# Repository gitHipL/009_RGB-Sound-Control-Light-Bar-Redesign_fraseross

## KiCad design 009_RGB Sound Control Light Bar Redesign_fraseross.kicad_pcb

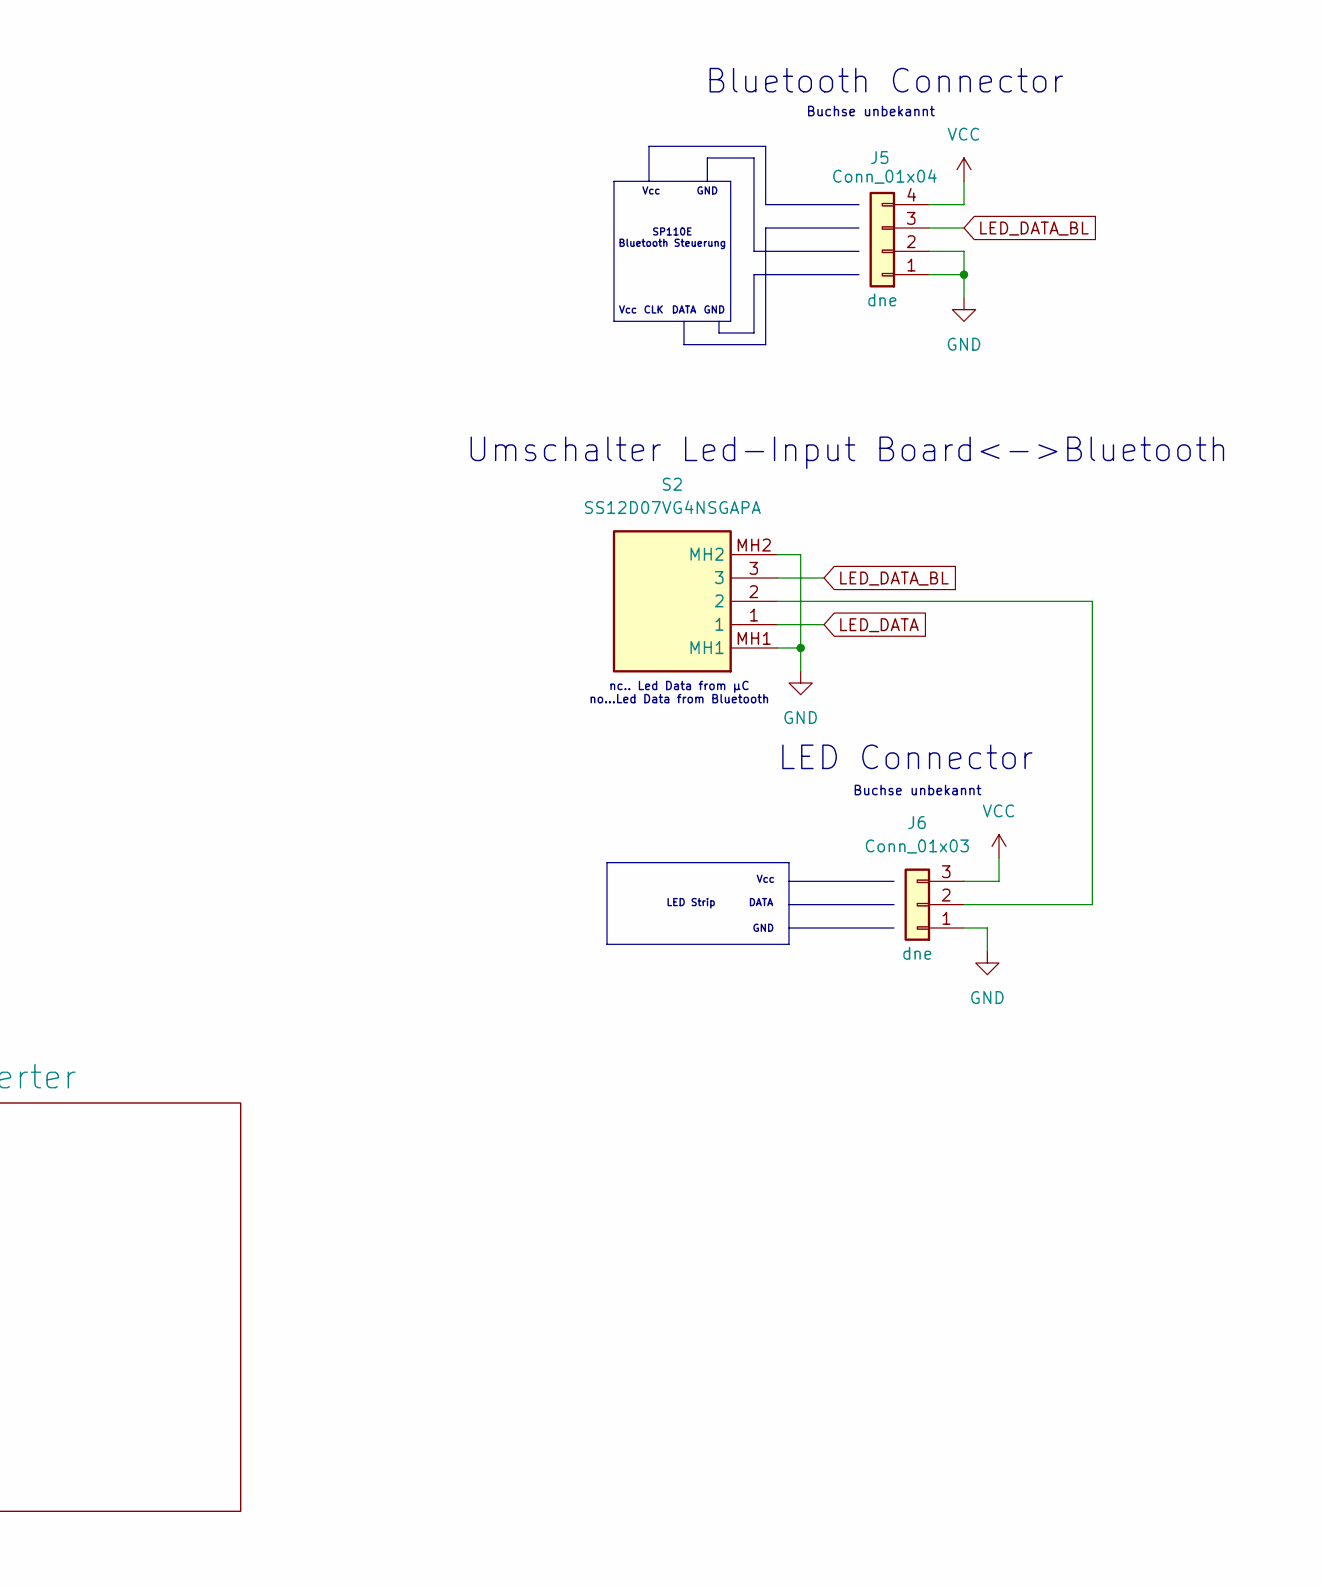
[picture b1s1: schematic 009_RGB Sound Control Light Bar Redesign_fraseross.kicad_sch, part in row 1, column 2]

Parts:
J5: Conn_01x04; PinSocket_1x04_P1.00mm_Vertical
J6: Conn_01x03; PinSocket_1x03_P1.00mm_Vertical
S2: SS12D07VG4NSGAPA; Manufacturer_Part_Number SS12D07VG4NSGAPA; Mouser Part Number N/A

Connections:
GND: J5.1, J5.2, J6.1, S2.MH1, S2.MH2; also elsewhere on the board
LED_DATA: S2.1; also elsewhere on the board
LED_DATA_BL: J5.3, S2.3
unnamed: J6.2, S2.2
VCC: J5.4, J6.3; also elsewhere on the board

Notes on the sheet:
Vcc
GND
Buchse unbekannt
LED Connector
Umschalter Led-Input Board<->Bluetooth
nc.. Led Data from µC no...Led Data from Bluetooth
DATA
CLK
Bluetooth Connector
SP110E Bluetooth Steuerung
LED Strip

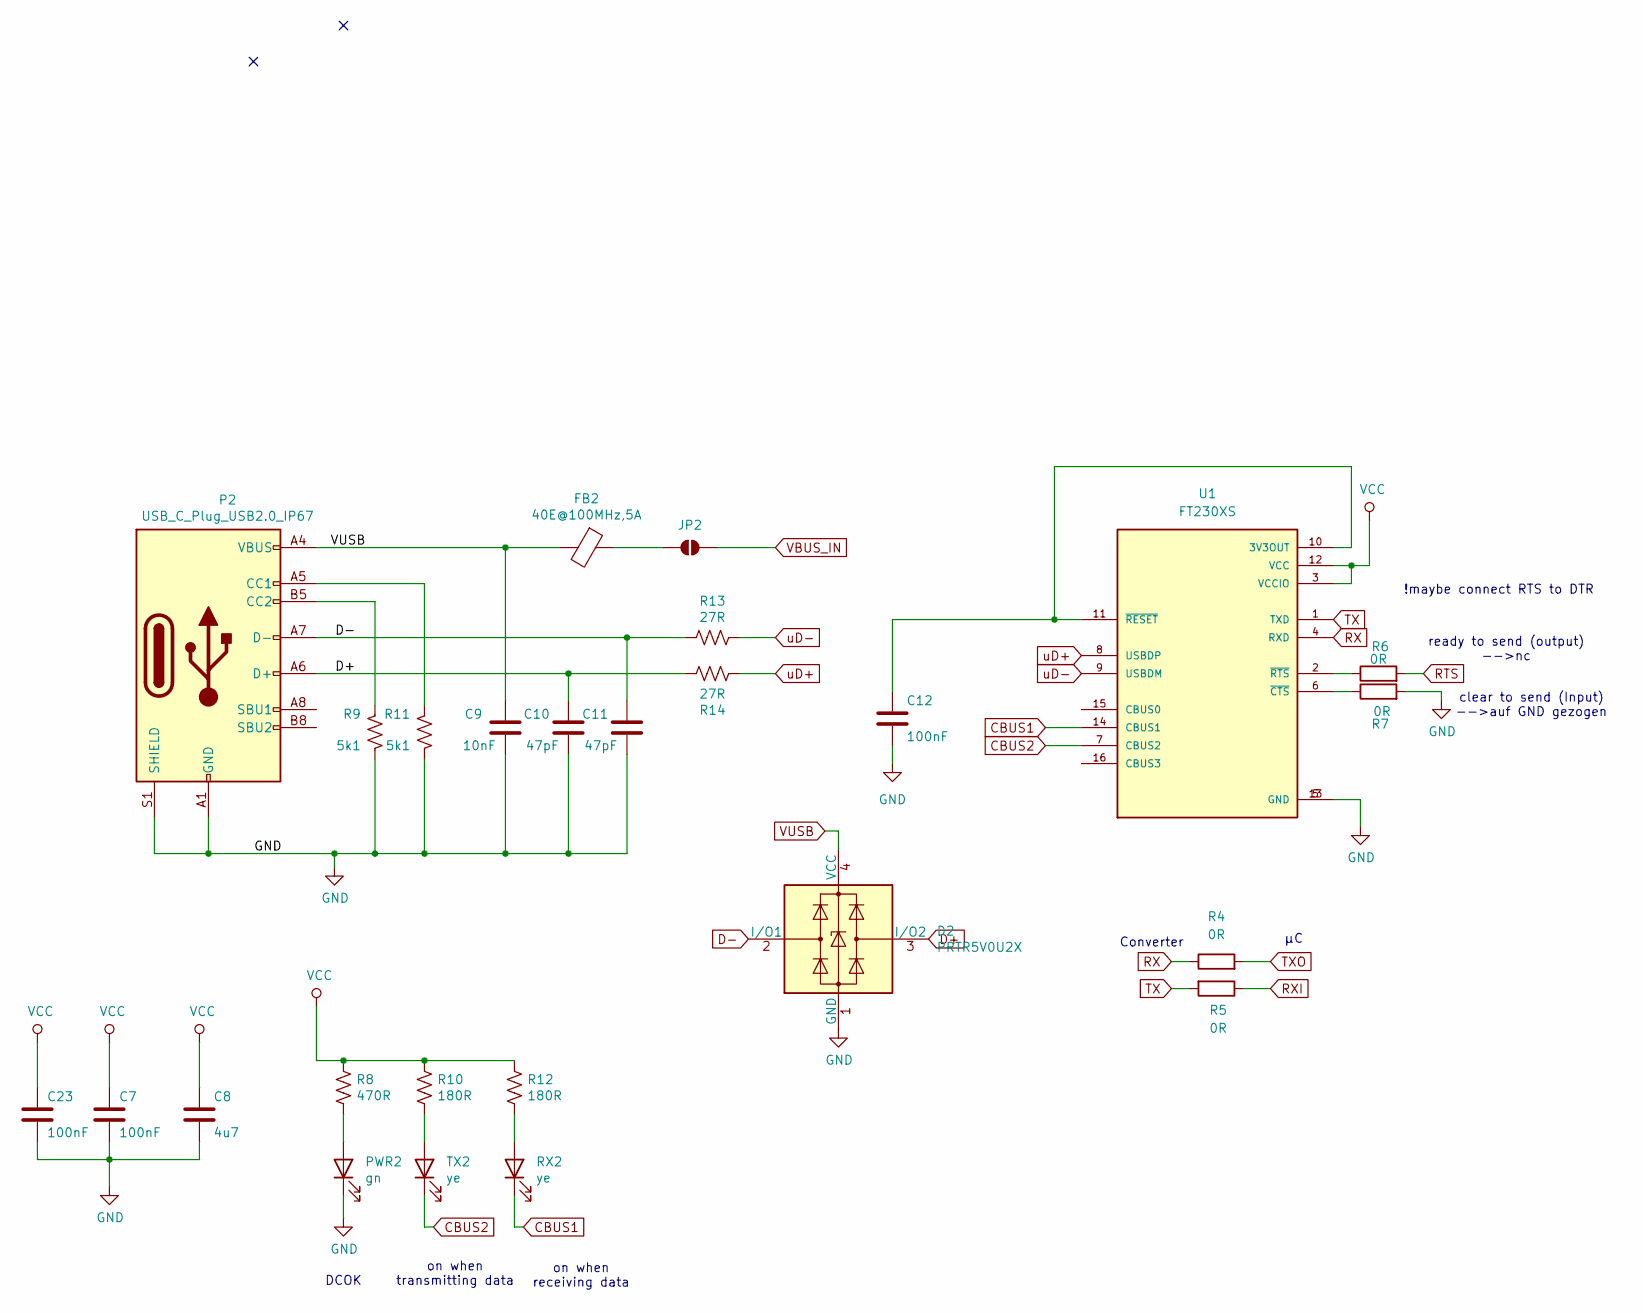
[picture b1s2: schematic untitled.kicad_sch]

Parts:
C7, C12, C23: 100nF; C_0603_1608Metric; Part C42998
C8: 4u7; C_0805_2012Metric; Part C87998
C9: 10nF; C_0603_1608Metric; Part C100042
C10, C11: 47pF; C_0603_1608Metric; Part C105622
D2: PRTR5V0U2X; SOT-143; LCSC PN C12333
FB2: 40E@100MHz,5A; L_0805_2012Metric; LCSC PN C369522
JP2: SolderJumper_2_Open; SolderJumper-2_P1.3mm_Bridged_RoundedPad1.0x1.5mm
P2: USB_C_Plug_USB2.0_IP67; GCT_USB4730-GF-A_REVA; Part USB4730-GF-A
PWR2: gn; LED_0603_1608Metric; LCSC PN C19171301
R4, R5, R6, R7: 0R; R_0603_1608Metric
R8: 470R; R_0603_1608Metric; LCSC C19171301
R9, R11: 5k1; R_0603_1608Metric; Part C332117
R10, R12: 180R; R_0603_1608Metric; Part C25585
R13, R14: 27R; R_0603_1608Metric; Part C325726
RX2: ye; LED_0603_1608Metric; LCSC PN C965802
TX2: ye; LED_0603_1608Metric; LCSC PN C965802
U1: FT230XS; SSOP-16_3.9x4.9mm_P0.635mm; PARTREV 1.5; LCSC PN C69082

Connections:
CBUS1: RX2.1 (K), U1.14 (CBUS1); also elsewhere on the board
CBUS2: TX2.1 (K), U1.7 (CBUS2); also elsewhere on the board
D+: C10.1, D2.3 (I/O2), P2.A6 (D+), P2.B6 (D+), R14.2
D-: C11.1, D2.2 (I/O1), P2.A7 (D-), P2.B7 (D-), R13.1
GND: C7.2, C8.2, C9.2, C10.2, C11.2, C12.2, C23.2, D2.1 (GND), P2.A1 (GND), P2.S1 (SHIELD), PWR2.1 (K), R7.2, R9.2, R11.2, U1.5 (GND), U1.13 (GND); also elsewhere on the board
unnamed: FB2.1, JP2.1 (A)
unnamed: P2.A5 (CC1), R11.1
unnamed: P2.B5 (CC2), R9.1
unnamed 32: PWR2.2 (A), R8.2; also elsewhere on the board
unnamed 33: R12.2, RX2.2 (A); also elsewhere on the board
unnamed 35: R10.2, TX2.2 (A); also elsewhere on the board
unnamed: C12.1, U1.10 (3V3OUT), U1.11 (~RESET)
unnamed: R7.1, U1.6 (~CTS)
unnamed: R6.1, U1.2 (~RTS)
RTS: R6.2; also elsewhere on the board
RX: R4.1, U1.4 (RXD)
RXI: R5.1; also elsewhere on the board
TX: R5.2, U1.1 (TXD)
TXO: R4.2; also elsewhere on the board
VBUS_IN: JP2.2 (B); also elsewhere on the board
VCC: C7.1, C8.1, C23.1, R8.1, R10.1, R12.1, U1.3 (VCCIO), U1.12 (VCC); also elsewhere on the board
VUSB: C9.1, D2.4 (VCC), FB2.2, P2.A4 (VBUS)
uD+: R14.1, U1.8 (USBDP)
uD-: R13.2, U1.9 (USBDM)

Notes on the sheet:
on when receiving data
DCOK
ready to send (output) -->nc
on when transmitting data
Converter
clear to send (Input) -->auf GND gezogen
!maybe connect RTS to DTR

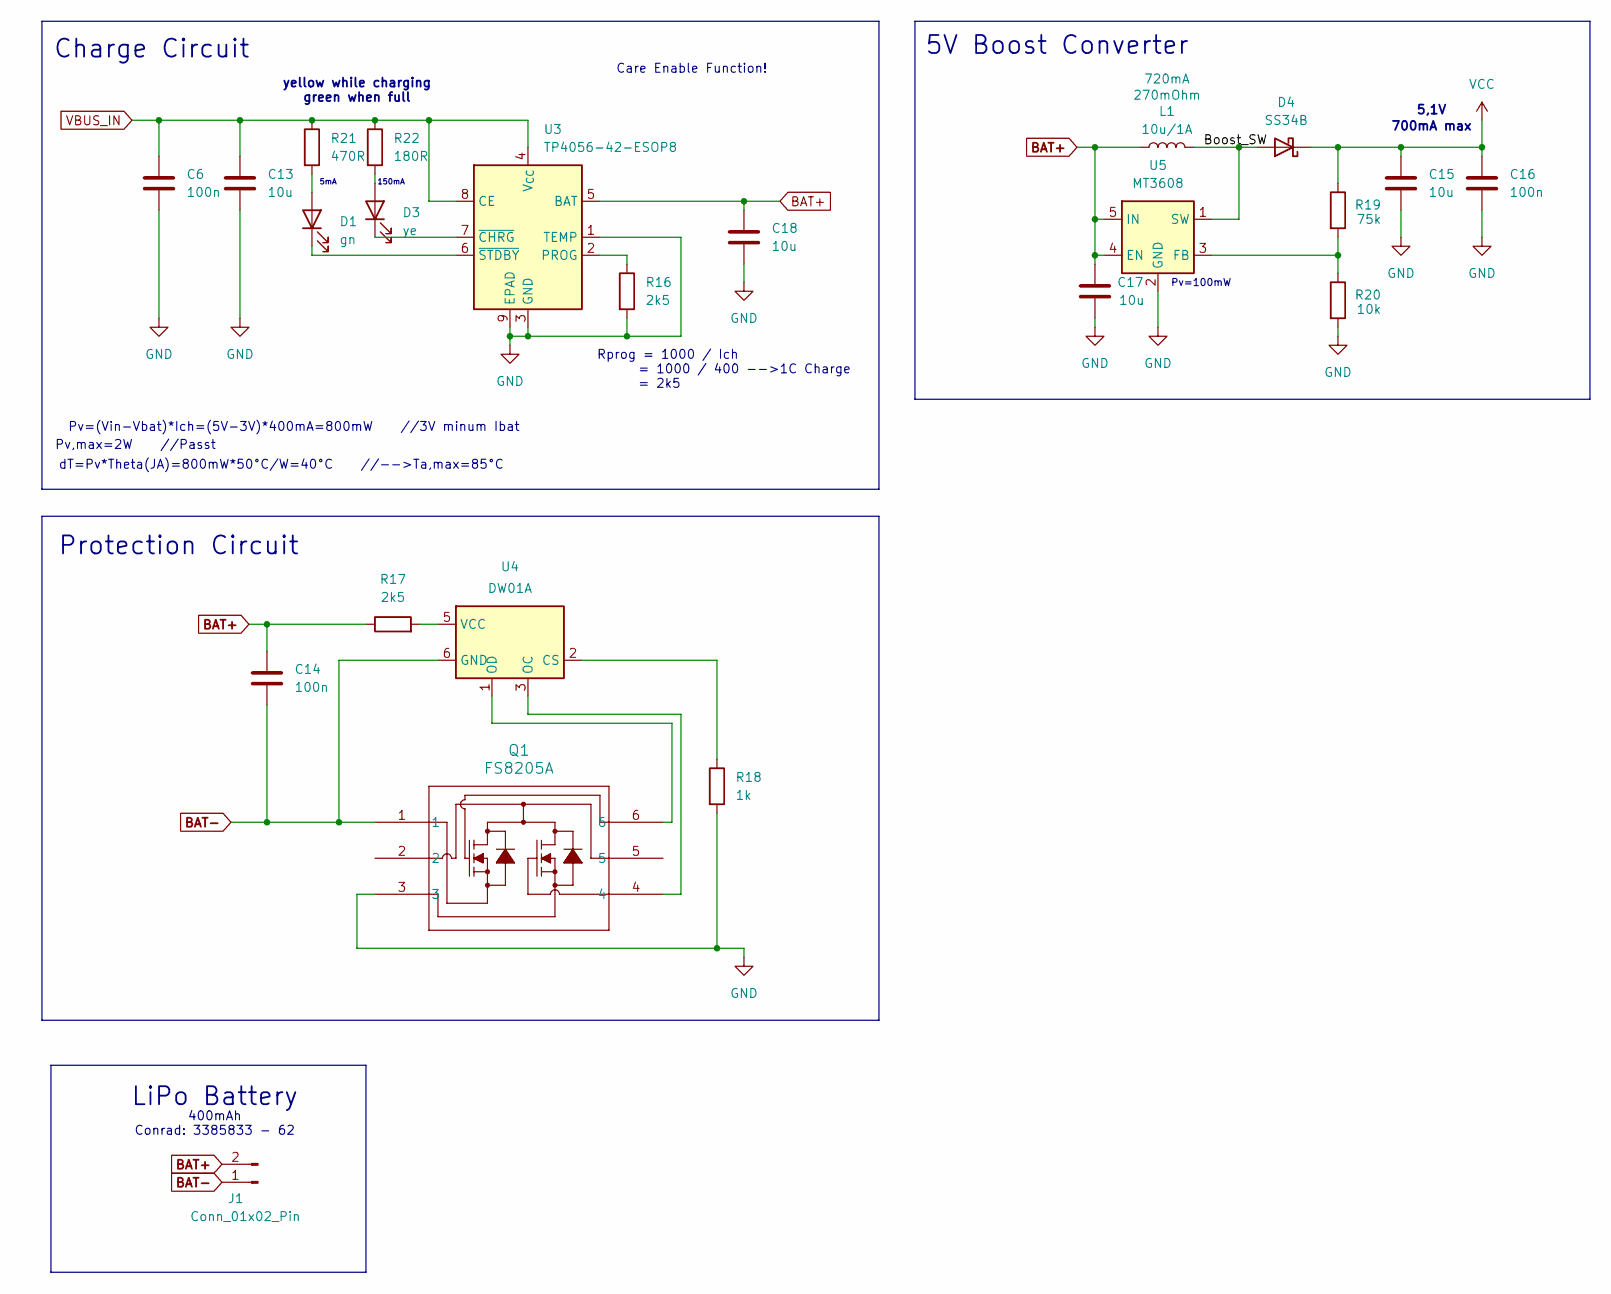
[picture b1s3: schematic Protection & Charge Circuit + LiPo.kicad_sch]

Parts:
C6, C14, C16: 100n; C_0603_1608Metric
C13, C18: 10u; C_0603_1608Metric
C15, C17: 10u; C_0805_2012Metric
D1: gn; LED_0603_1608Metric; LCSC PN C19171301
D3: ye; LED_0603_1608Metric; LCSC PN C965802
D4: SS34B; D_SMB; LCSC PN C13762
J1: Conn_01x02_Pin; PinHeader_1x02_P2.54mm_Vertical
L1: 10u/1A; L_Coilcraft_LPS3010; LCSC C280522
Q1: FS8205A; SOT-23-6; LCSC PN C2830320
R16: 2k5; R_0603_1608Metric
R17: 2k5; R_0805_2012Metric
R18: 1k; R_0603_1608Metric
R19: 75k; R_0603_1608Metric
R20: 10k; R_0603_1608Metric
R21: 470R; R_0603_1608Metric
R22: 180R; R_0603_1608Metric
U3: TP4056-42-ESOP8; SOIC-8-1EP_3.9x4.9mm_P1.27mm_EP2.41x3.3mm_ThermalVias; LCSC PN C725790
U4: DW01A; SOT-23-6; LCSC PN C2927799
U5: MT3608; SOT-23-6; LCSC PN C84817

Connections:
/Power/Boost_SW: D4.2 (A), L1.2, U5.1 (SW)
BAT+: C14.2, C17.1, C18.2, J1.2, L1.1, R17.1, U3.5 (BAT), U5.4 (EN), U5.5 (IN)
BAT-: C14.1, J1.1, Q1.1, U4.6 (GND)
GND: C6.1, C13.1, C15.2, C16.2, C17.2, C18.1, Q1.3, R16.2, R18.2, R20.2, U3.1 (TEMP), U3.3 (GND), U3.9 (EPAD), U5.2 (GND); also elsewhere on the board
unnamed: D1.2 (A), R21.2
unnamed: D1.1 (K), U3.6 (~STDBY)
unnamed: D3.2 (A), R22.2
unnamed: D3.1 (K), U3.7 (~CHRG)
unnamed: R16.1, U3.2 (PROG)
unnamed: R18.1, U4.2 (CS)
unnamed: Q1.4, U4.3 (OC)
unnamed: Q1.6, U4.1 (OD)
unnamed: R17.2, U4.5 (VCC)
unnamed: R19.2, R20.1, U5.3 (FB)
VBUS_IN: C6.2, C13.2, R21.1, R22.1, U3.4 (V_{CC}), U3.8 (CE); also elsewhere on the board
VCC: C15.1, C16.1, D4.1 (K), R19.1; also elsewhere on the board

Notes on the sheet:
400mAh Conrad: 3385833 - 62
LiPo Battery
dT=Pv*Theta(JA)=800mW*50°C/W=40°C //-->Ta,max=85°C
yellow while charging green when full
Rprog = 1000 / Ich = 1000 / 400 -->1C Charge = 2k5
5mA
5V Boost Converter
150mA
Pv=100mW
5,1V
700mA max
Protection Circuit
Care Enable Function!
Pv,max=2W //Passt
Charge Circuit
Pv=(Vin-Vbat)*Ich=(5V-3V)*400mA=800mW //3V minum Ibat

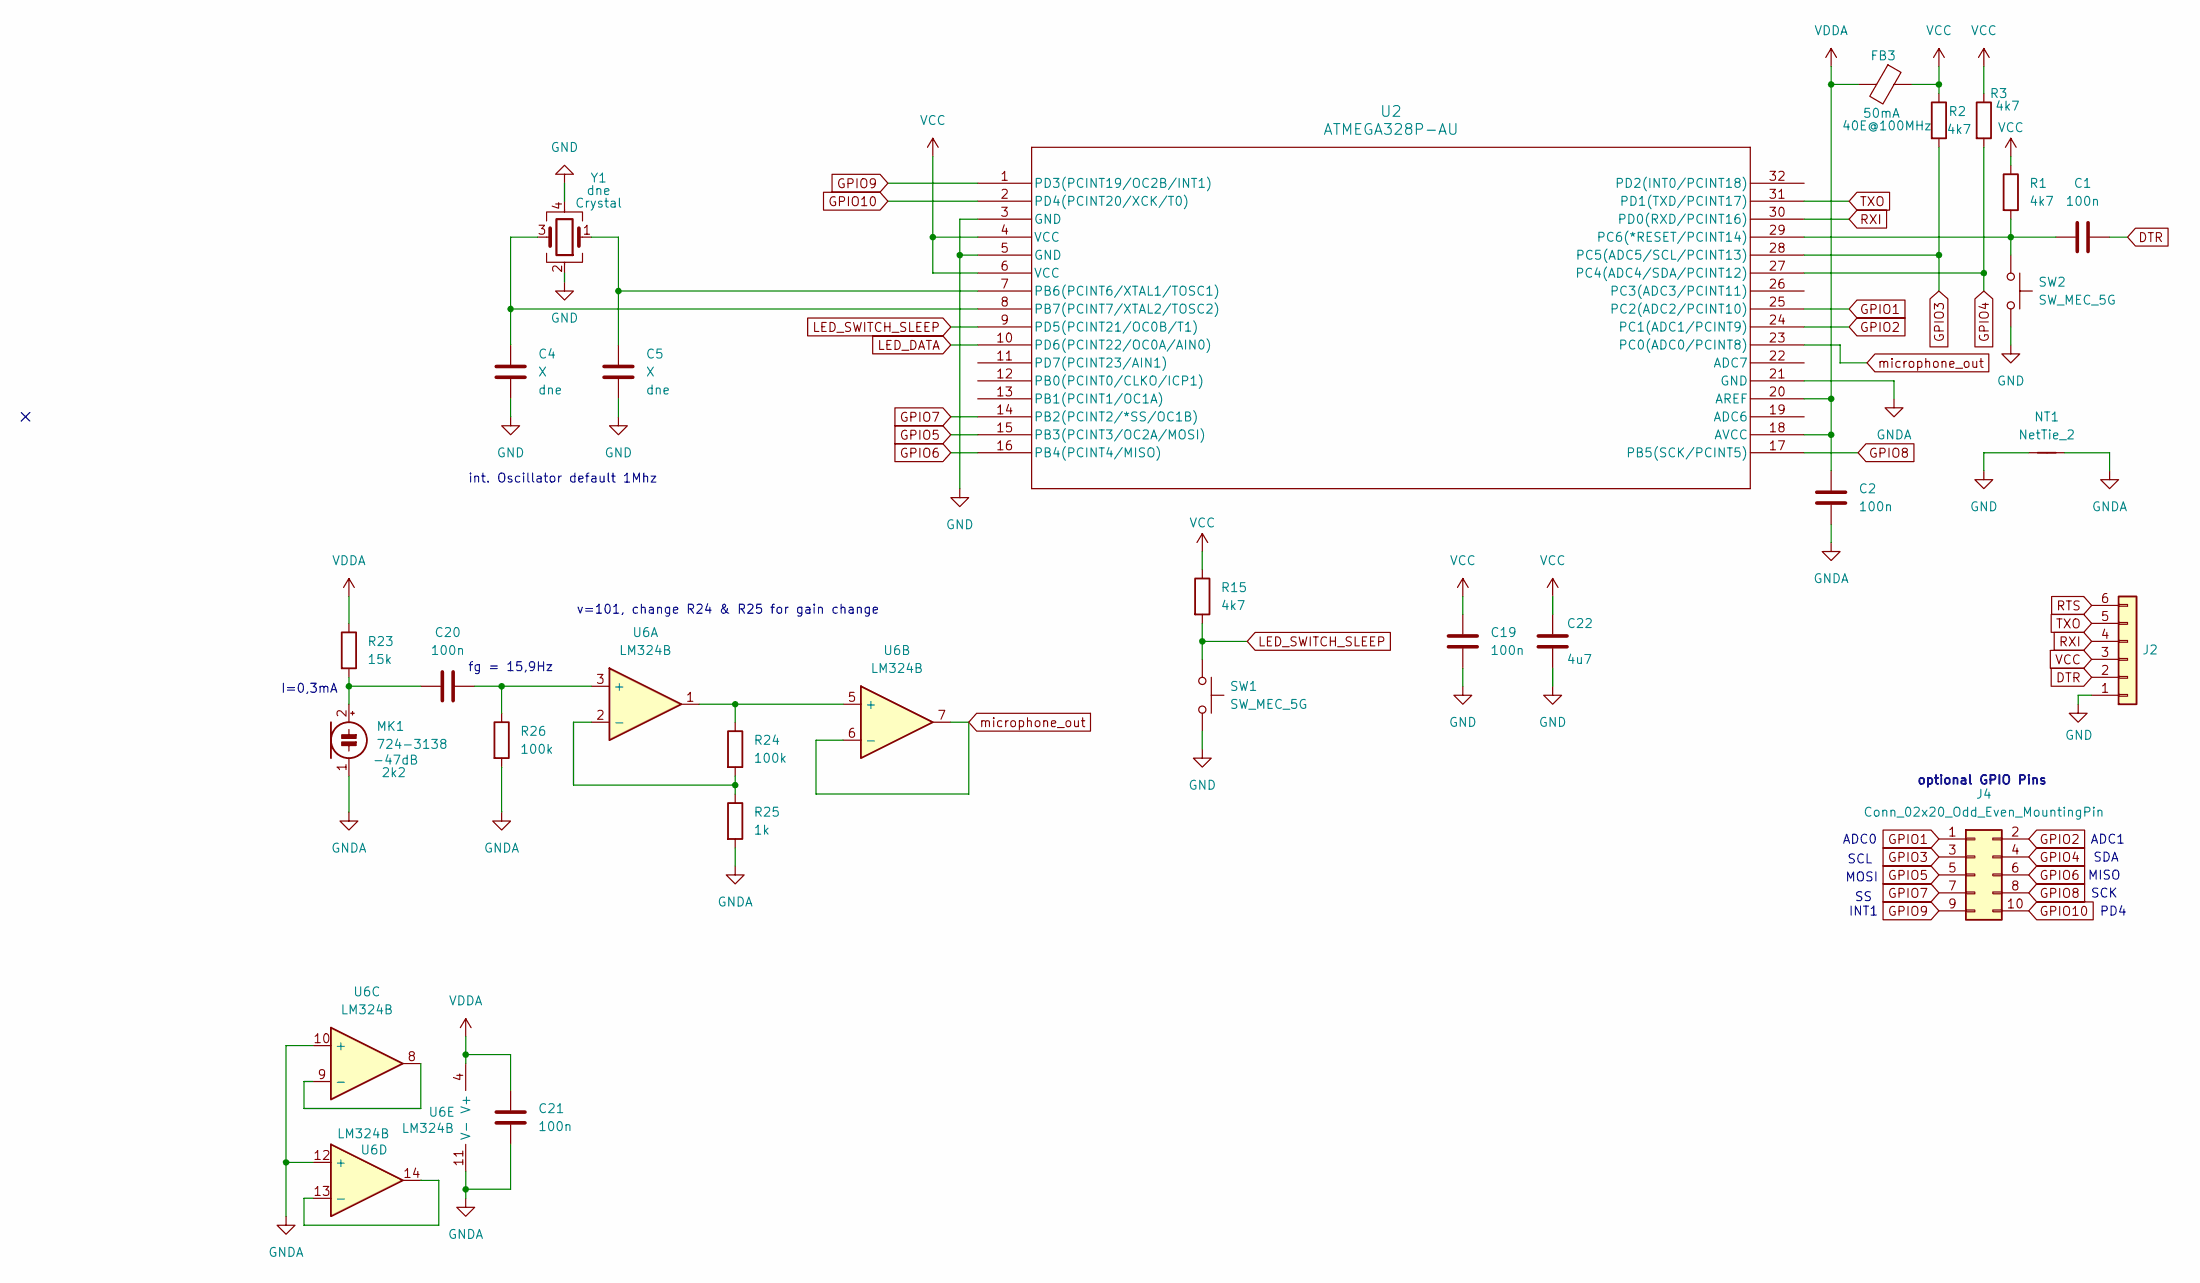
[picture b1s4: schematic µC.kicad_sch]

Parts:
C1, C2, C19, C20, C21: 100n; C_0603_1608Metric
C4, C5: X; C_0603_1608Metric
C22: 4u7; C_0805_2012Metric; Part C87998
FB3: 40E@100MHz; L_0603_1608Metric; LCSC PN C142073
J2: Conn_01x06; PinHeader_1x06_P2.54mm_Vertical
J4: Conn_02x20_Odd_Even_MountingPin; PinHeader_2x05_P1.00mm_Vertical_SMD
MK1: 724-3138; 724-3138 microphone RS Components
NT1: NetTie_2; NetTie-2_SMD_Pad0.5mm
R1, R2, R3, R15: 4k7; R_0603_1608Metric
R23: 15k; R_0603_1608Metric
R24, R26: 100k; R_0603_1608Metric
R25: 1k; R_0603_1608Metric
SW1: SW_MEC_5G; SW_K2-1112SW-A4SW-04_HRO; LCSC PN C223811
SW2: SW_MEC_5G; SW_Taster_C381039; LCSC C381039
U2: ATMEGA328P-AU; TQFP32_32A_MCH; LCSC PN C14877
U6: LM324B; TSSOP-14_4.4x5mm_P0.65mm; LCSC PN C5214225
Y1: Crystal; Crystal_SMD_Abracon_ABM8AIG-4Pin_3.2x2.5mm; LCSC PN C13738

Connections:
DTR: C1.2, J2.2
GND: C4.1, C5.1, C19.1, C22.2, J2.1, NT1.1, SW1.2 (B), SW2.2 (B), U2.3 (GND), U2.5 (GND), Y1.2, Y1.4; also elsewhere on the board
GNDA: C2.1, C21.1, MK1.1 (-), NT1.2, R25.2, R26.2, U2.21 (GND), U6.10 (+), U6.11 (V-), U6.12 (+)
GPIO1: J4.1, U2.25 (PC2(ADC2/PCINT10))
GPIO2: J4.2, U2.24 (PC1(ADC1/PCINT9))
GPIO3: J4.3, R2.2, U2.28 (PC5(ADC5/SCL/PCINT13))
GPIO4: J4.4, R3.2, U2.27 (PC4(ADC4/SDA/PCINT12))
GPIO5: J4.5, U2.15 (PB3(PCINT3/OC2A/MOSI))
GPIO6: J4.6, U2.16 (PB4(PCINT4/MISO))
GPIO7: J4.7, U2.14 (PB2(PCINT2/*SS/OC1B))
GPIO8: J4.8, U2.17 (PB5(SCK/PCINT5))
GPIO9: J4.9, U2.1 (PD3(PCINT19/OC2B/INT1))
GPIO10: J4.10, U2.2 (PD4(PCINT20/XCK/T0))
LED_DATA: U2.10 (PD6(PCINT22/OC0A/AIN0)); also elsewhere on the board
LED_SWITCH_SLEEP: R15.2, SW1.1 (A), U2.9 (PD5(PCINT21/OC0B/T1))
unnamed: C20.1, MK1.2 (+), R23.2
unnamed: C1.1, R1.2, SW2.1 (A), U2.29 (PC6(*RESET/PCINT14))
unnamed: C5.2, U2.7 (PB6(PCINT6/XTAL1/TOSC1)), Y1.1
unnamed: C4.2, U2.8 (PB7(PCINT7/XTAL2/TOSC2)), Y1.3
unnamed: C20.2, R26.1, U6.3 (+)
unnamed: R24.2, R25.1, U6.2 (-)
unnamed: R24.1, U6.1, U6.5 (+)
unnamed: U6.8, U6.9 (-)
unnamed: U6.13 (-), U6.14
RTS: J2.6; also elsewhere on the board
RXI: J2.4, U2.30 (PD0(RXD/PCINT16)); also elsewhere on the board
TXO: J2.5, U2.31 (PD1(TXD/PCINT17)); also elsewhere on the board
VCC: C19.2, C22.1, FB3.1, J2.3, R1.1, R2.1, R3.1, R15.1, U2.4 (VCC), U2.6 (VCC); also elsewhere on the board
VDDA: C2.2, C21.2, FB3.2, R23.1, U2.18 (AVCC), U2.20 (AREF), U6.4 (V+)
microphone_out: U2.23 (PC0(ADC0/PCINT8)), U6.6 (-), U6.7

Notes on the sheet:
SCL
I=0,3mA
INT1
ADC1
PD4
SDA
optional GPIO Pins
v=101, change R24 & R25 for gain change
MISO
ADC0
int. Oscillator default 1Mhz
fg = 15,9Hz
MOSI
SCK

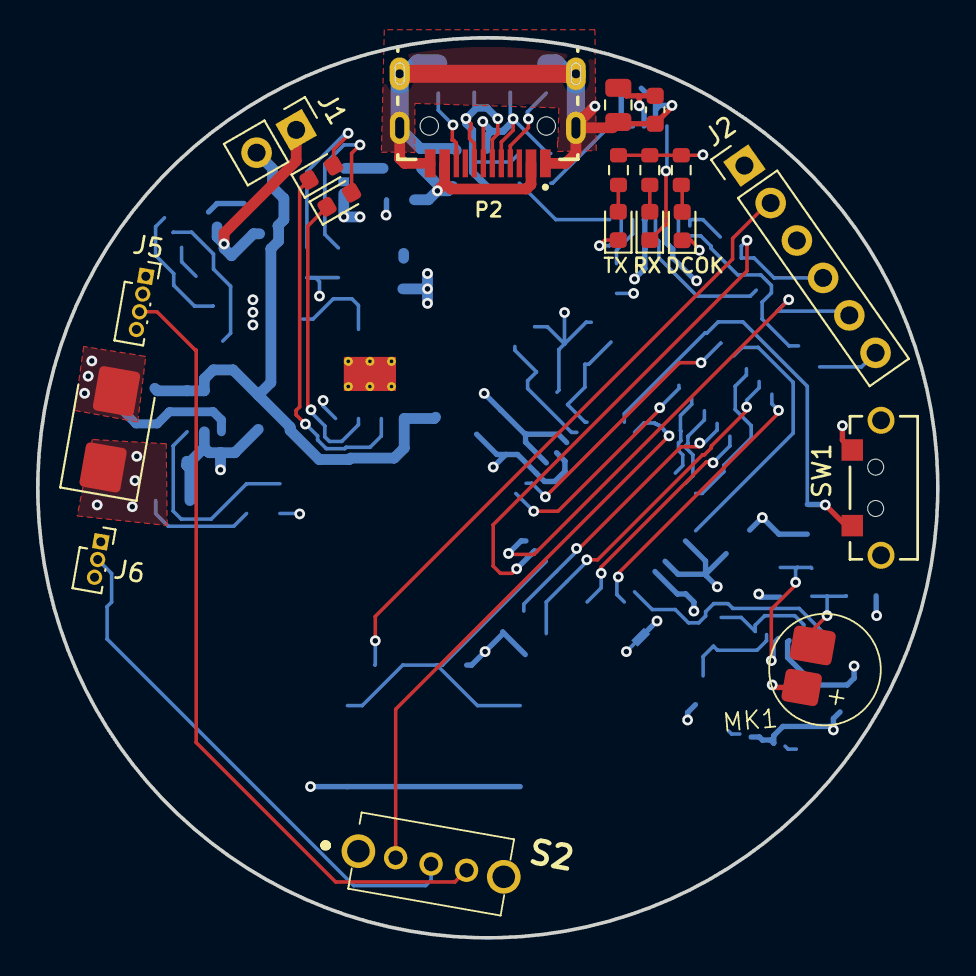
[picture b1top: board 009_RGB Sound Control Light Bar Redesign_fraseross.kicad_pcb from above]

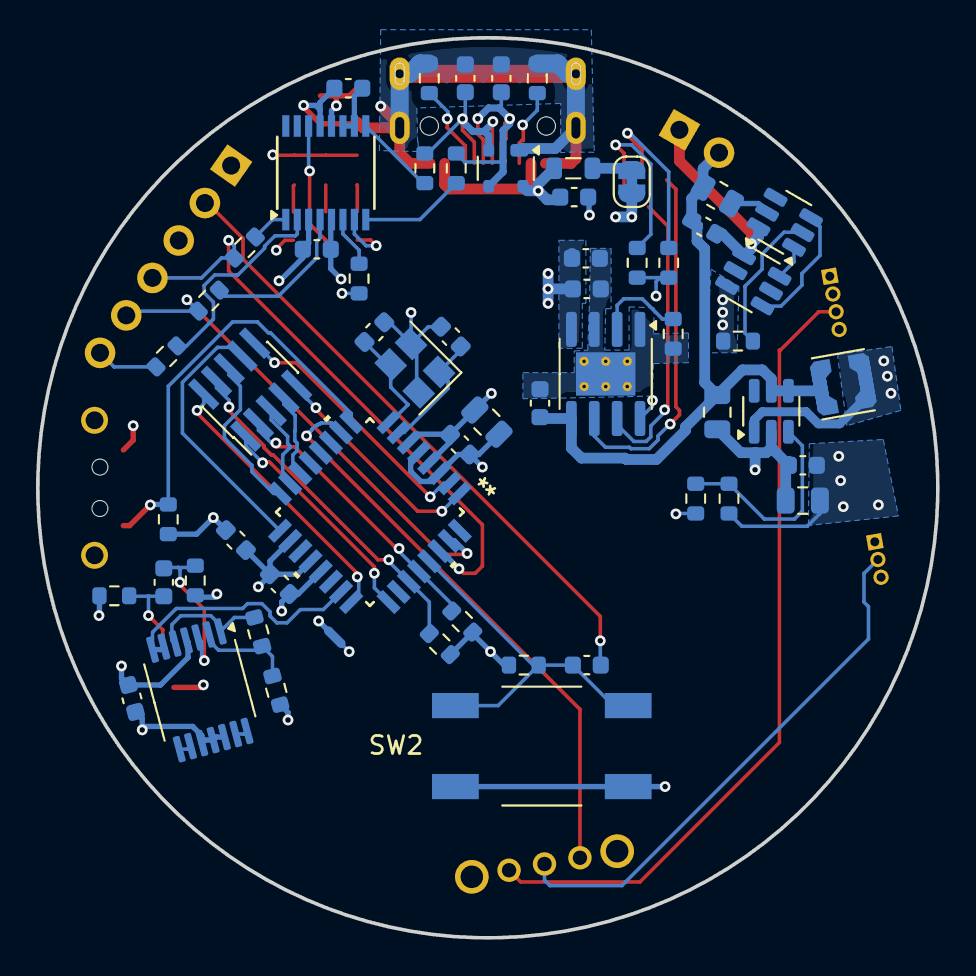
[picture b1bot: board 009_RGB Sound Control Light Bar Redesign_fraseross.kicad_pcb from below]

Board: 4 copper layers, 50.0 x 50.0 mm, 78 parts (59 on the bottom side), 64 nets.

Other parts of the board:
DCOK: gn; LED_0603_1608Metric
RX: ye; LED_0603_1608Metric
TX: ye; LED_0603_1608Metric

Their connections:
CBUS1: RX.1 (K); also elsewhere on the board
CBUS2: TX.1 (K); also elsewhere on the board
GND: DCOK.1 (K); also elsewhere on the board
unnamed 32: DCOK.2 (A); also elsewhere on the board
unnamed 33: RX.2 (A); also elsewhere on the board
unnamed 35: TX.2 (A); also elsewhere on the board

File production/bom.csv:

Designator,Footprint,Quantity,Value,LCSC Part #
"C1, C14, C16, C19, C2, C20, C21, C6",0603,8,100n,
"C10, C11",0603,2,47pF,
"C12, C23, C7",0603,3,100nF,
"C13, C18",0603,2,10u,
"C15, C17",0805,2,10u,
"C22, C8",0805,2,4u7,
"C4, C5",0603,2,X,
C9,0603,1,10nF,
D1,0603,1,gn,C19171301
D2,SOT-143,1,PRTR5V0U2X, C12333
"D3, RX, TX",0603,3,ye,C965802
D4,D_SMB,1,SS34B,C13762
DCOK,0603,1,gn,
FB2,0805,1,"40E@100MHz,5A",
FB3,0603,1,40E@100MHz,C285651
J1,PinHeader_1x02_P2.54mm_Vertical,1,Conn_01x02_Pin,
J2,PinHeader_1x06_P2.54mm_Vertical,1,Conn_01x06,
J4,PinHeader_2x05_P1.00mm_Vertical_SMD,1,Conn_02x20_Odd_Even_MountingPin,
J5,PinSocket_1x04_P1.00mm_Vertical,1,Conn_01x04,
J6,PinSocket_1x03_P1.00mm_Vertical,1,Conn_01x03,
JP2,SolderJumper-2_P1.3mm_Bridged_RoundedPad1.0x1.5mm,1,SolderJumper_2_Open,
L1,L_Coilcraft_LPS3010,1,10u/1A,C280522
MK1,724-3138 microphone RS Components,1,724-3138,
P2,GCT_USB4730-GF-A_REVA,1,USB_C_Plug_USB2.0_IP67,
Q1,SOT-23-6,1,FS8205A,C2830320
"R1, R15, R2, R3",0603,4,4k7,
"R10, R12, R22",0603,3,180R,
"R11, R9",0603,2,5k1,
"R13, R14",0603,2,27R,
R16,0603,1,2k5,
R17,0805,1,2k5,
"R18, R25",0603,2,1k,
R19,0603,1,75k,
R20,0603,1,10k,
R21,0603,1,480R,
R23,0603,1,15k,
"R24, R26",0603,2,100k,
"R4, R5, R6, R7",0603,4,0R,
R8,0603,1,480R,C19171301
S2,SS12D07VG4NSGAPA,1,SS12D07VG4NSGAPA,C2939726
SW1,SW_K2-1112SW-A4SW-04_HRO,1,SW_MEC_5G,C381039
SW2,SW_Taster_C381039,1,SW_MEC_5G,C381039
U1,SSOP-16_3.9x4.9mm_P0.635mm,1,FT230XS,C69082
U2,TQFP32_32A_MCH,1,ATMEGA328P-AU,C14877
U3,SOIC-8-1EP_3.9x4.9mm_P1.27mm_EP2.41x3.3mm_ThermalVias,1,TP4056-42-ESOP8,C725790
U4,SOT-23-6,1,DW01A,C2927799
U5,SOT-23-6,1,MT3608,C84817
U6,TSSOP-14_4.4x5mm_P0.65mm,1,LM324B,C5214225
Y1,Crystal_SMD_Abracon_ABM8AIG-4Pin_3.2x2.5mm,1,Crystal,C13738

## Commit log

2025-05-21 Init
